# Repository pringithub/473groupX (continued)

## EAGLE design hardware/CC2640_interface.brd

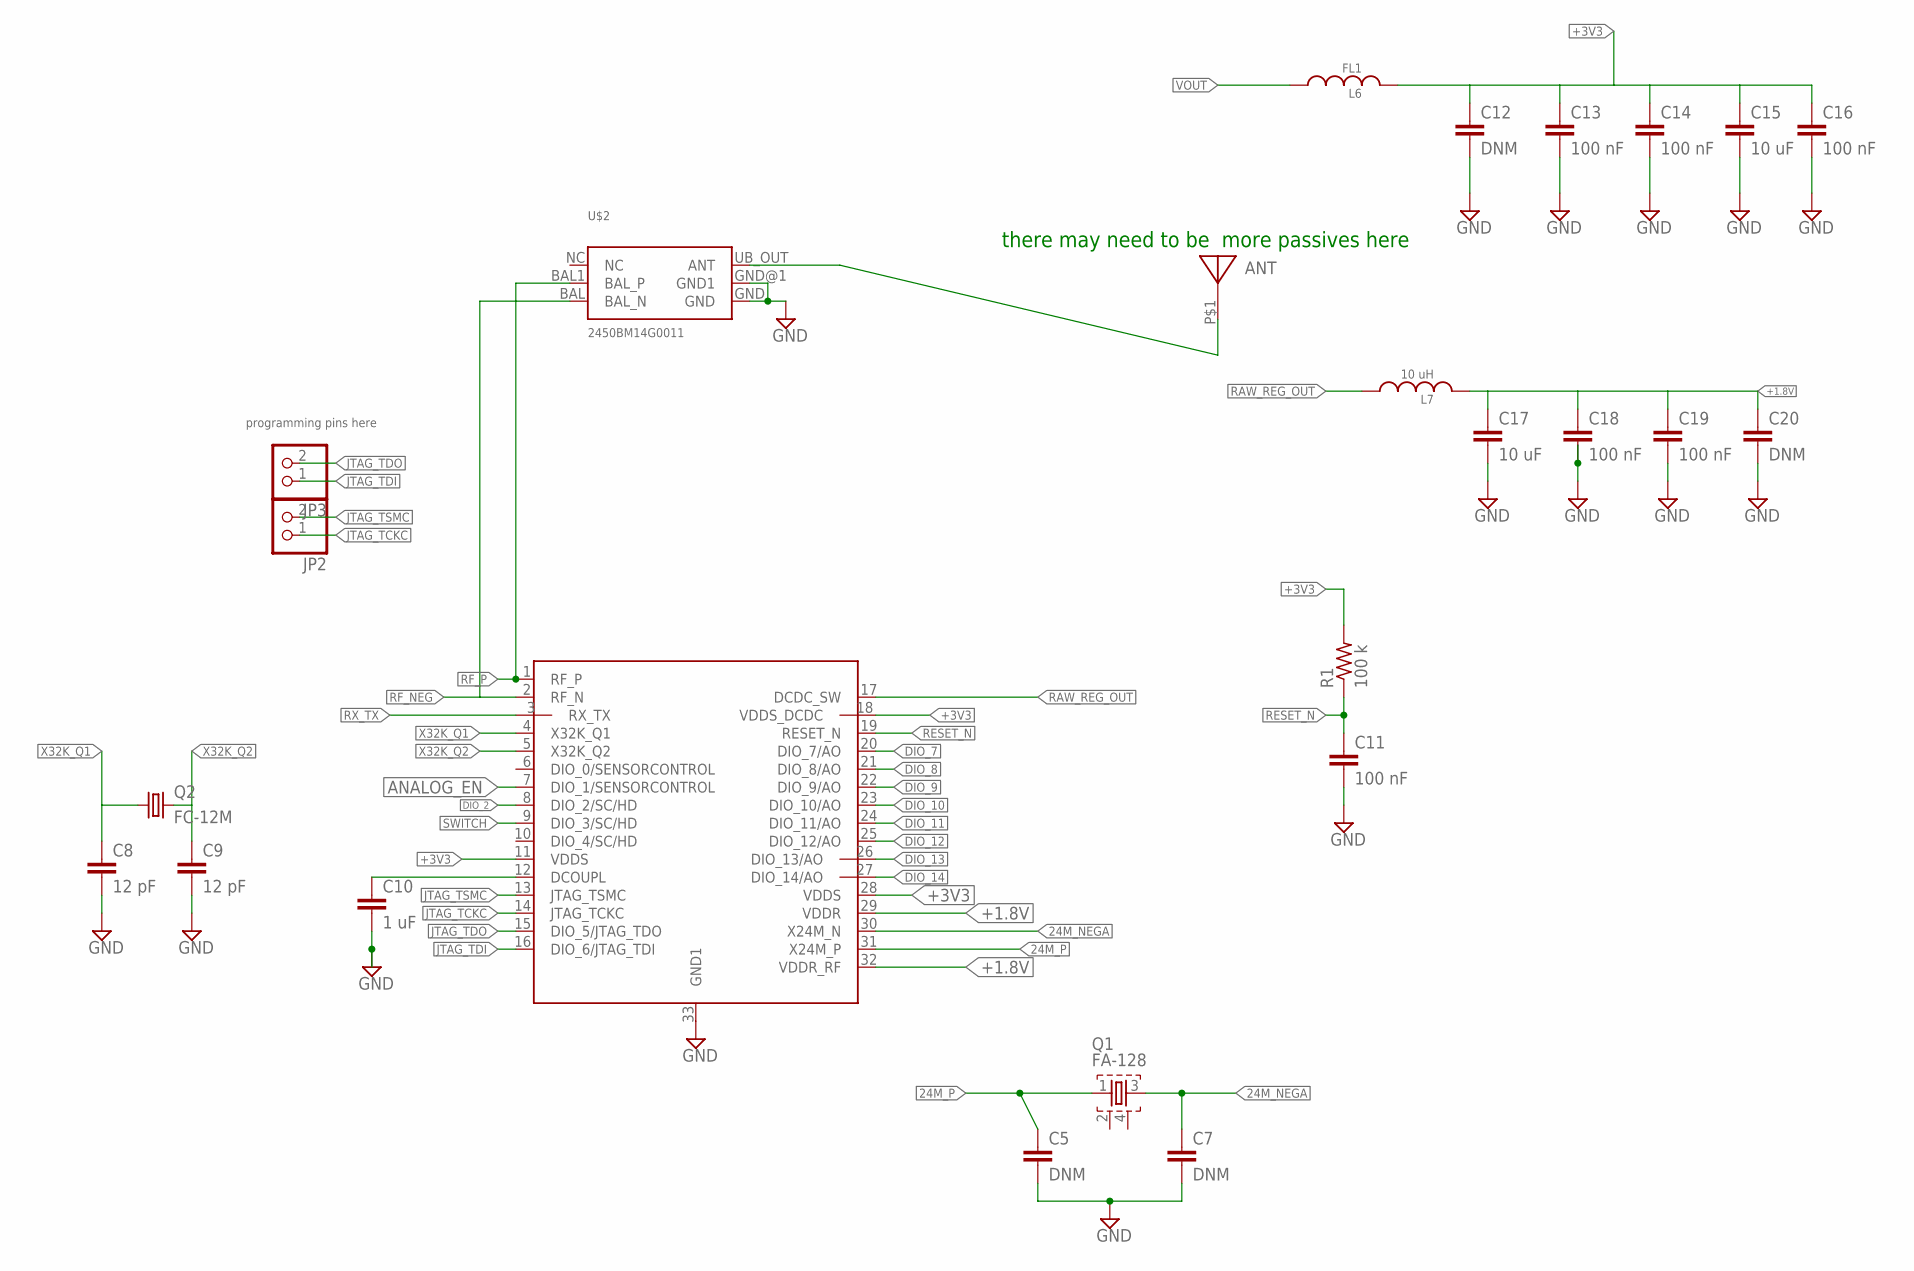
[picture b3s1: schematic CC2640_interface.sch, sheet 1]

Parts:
ANT: 2450AT18A100
C5, C7, C12, C20: DNM; C0402
C8, C9: 12 pF; C0402
C10: 1 uF; C0402
C11, C13, C14, C16, C18, C19: 100 nF; C0402
C15, C17: 10 uF; C0402
JP2, JP3: PINHD-1X2; 1X02
L6: FL1; 0603_CAP
L7: 10 uH; 0603_CAP
Q1: FA-128
Q2: FC-12M
R1: 100 k; R0402@1
U$1: CC2640-5MM; S-PVQFN-N32
U$2: 2450BM14G0011; DFN/LCC-6

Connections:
24M_NEGA: C7.1, Q1.3, U$1.30 (X24M_N)
24M_P: C5.1, Q1.1, U$1.31 (X24M_P)
+1.8V: C17.1, C18.1, C19.1, C20.1, L7.2, U$1.29 (VDDR), U$1.32 (VDDR_RF)
+3V3: C12.1, C13.1, C14.1, C15.1, C16.1, L6.2, R1.2, U$1.11 (VDDS), U$1.18 (VDDS_DCDC), U$1.28 (VDDS); also elsewhere on the board
ANALOG_EN: U$1.7 (DIO_1/SENSORCONTROL); also elsewhere on the board
DCOUPLE_ME: C10.1, U$1.12 (DCOUPL)
DIO_2: U$1.8 (DIO_2/SC/HD); also elsewhere on the board
DIO_7: U$1.20 (DIO_7/AO)
DIO_8: U$1.21 (DIO_8/AO)
DIO_9: U$1.22 (DIO_9/AO); also elsewhere on the board
DIO_10: U$1.23 (DIO_10/AO); also elsewhere on the board
DIO_11: U$1.24 (DIO_11/AO); also elsewhere on the board
DIO_12: U$1.25 (DIO_12/AO); also elsewhere on the board
DIO_13: U$1.26 (DIO_13/AO)
DIO_14: U$1.27 (DIO_14/AO); also elsewhere on the board
GND: C5.2, C7.2, C8.2, C9.2, C10.2, C11.2, C12.2, C13.2, C14.2, C15.2, C16.2, C17.2, C18.2, C19.2, C20.2, U$1.33 (GND1), U$2.GND, U$2.GND@1 (GND1); also elsewhere on the board
JTAG_TCKC: JP2.1, U$1.14 (JTAG_TCKC)
JTAG_TDI: JP3.1, U$1.16 (DIO_6/JTAG_TDI)
JTAG_TDO: JP3.2, U$1.15 (DIO_5/JTAG_TDO)
JTAG_TSMC: JP2.2, U$1.13 (JTAG_TSMC)
unnamed: ANT.P$1, U$2.UB_OUT (ANT)
RAW_REG_OUT: L7.1, U$1.17 (DCDC_SW)
RESET_N: C11.1, R1.1, U$1.19 (RESET_N)
RF_NEG: U$1.2 (RF_N), U$2.BAL (BAL_N)
RF_P: U$1.1 (RF_P), U$2.BAL1 (BAL_P)
RX_TX: U$1.3 (RX_TX)
SWITCH: U$1.9 (DIO_3/SC/HD); also elsewhere on the board
VOUT: L6.1; also elsewhere on the board
X32K_Q1: C8.1, Q2.1, U$1.4 (X32K_Q1)
X32K_Q2: C9.1, Q2.2, U$1.5 (X32K_Q2)

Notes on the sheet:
there may need to be more passives here
programming pins here

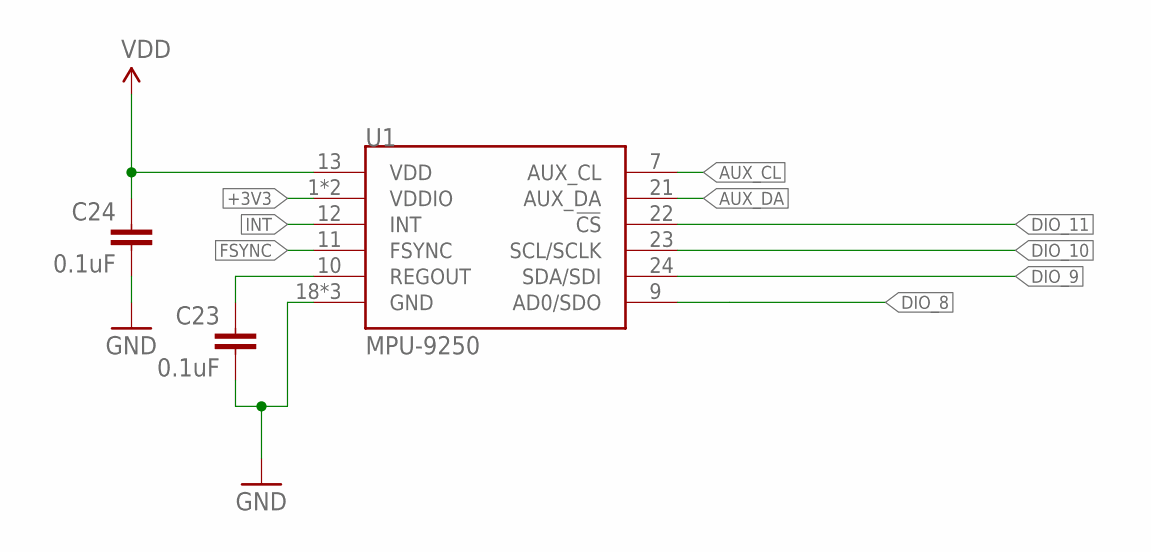
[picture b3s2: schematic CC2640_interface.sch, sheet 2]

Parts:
C23, C24: 0.1uF; 0603-CAP
U1: MPU-9250; QFN24_PAD

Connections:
+3V3: C24.1, U1.1 (VDDIO), U1.8 (VDDIO), U1.13 (VDD); also elsewhere on the board
ADSD_STUB: U1.9 (AD0/SDO)
AUX_CL: U1.7 (AUX_CL)
AUX_DA: U1.21 (AUX_DA)
DIO_9: U1.24 (SDA/SDI); also elsewhere on the board
DIO_10: U1.23 (SCL/SCLK); also elsewhere on the board
DIO_11: U1.22 (!CS); also elsewhere on the board
FSYNC: U1.11 (FSYNC)
GND: C23.2, C24.2, U1.18 (GND), U1.20 (GND), U1.CENTER (GND); also elsewhere on the board
INT: U1.12 (INT)
REGOUT: C23.1, U1.10 (REGOUT)

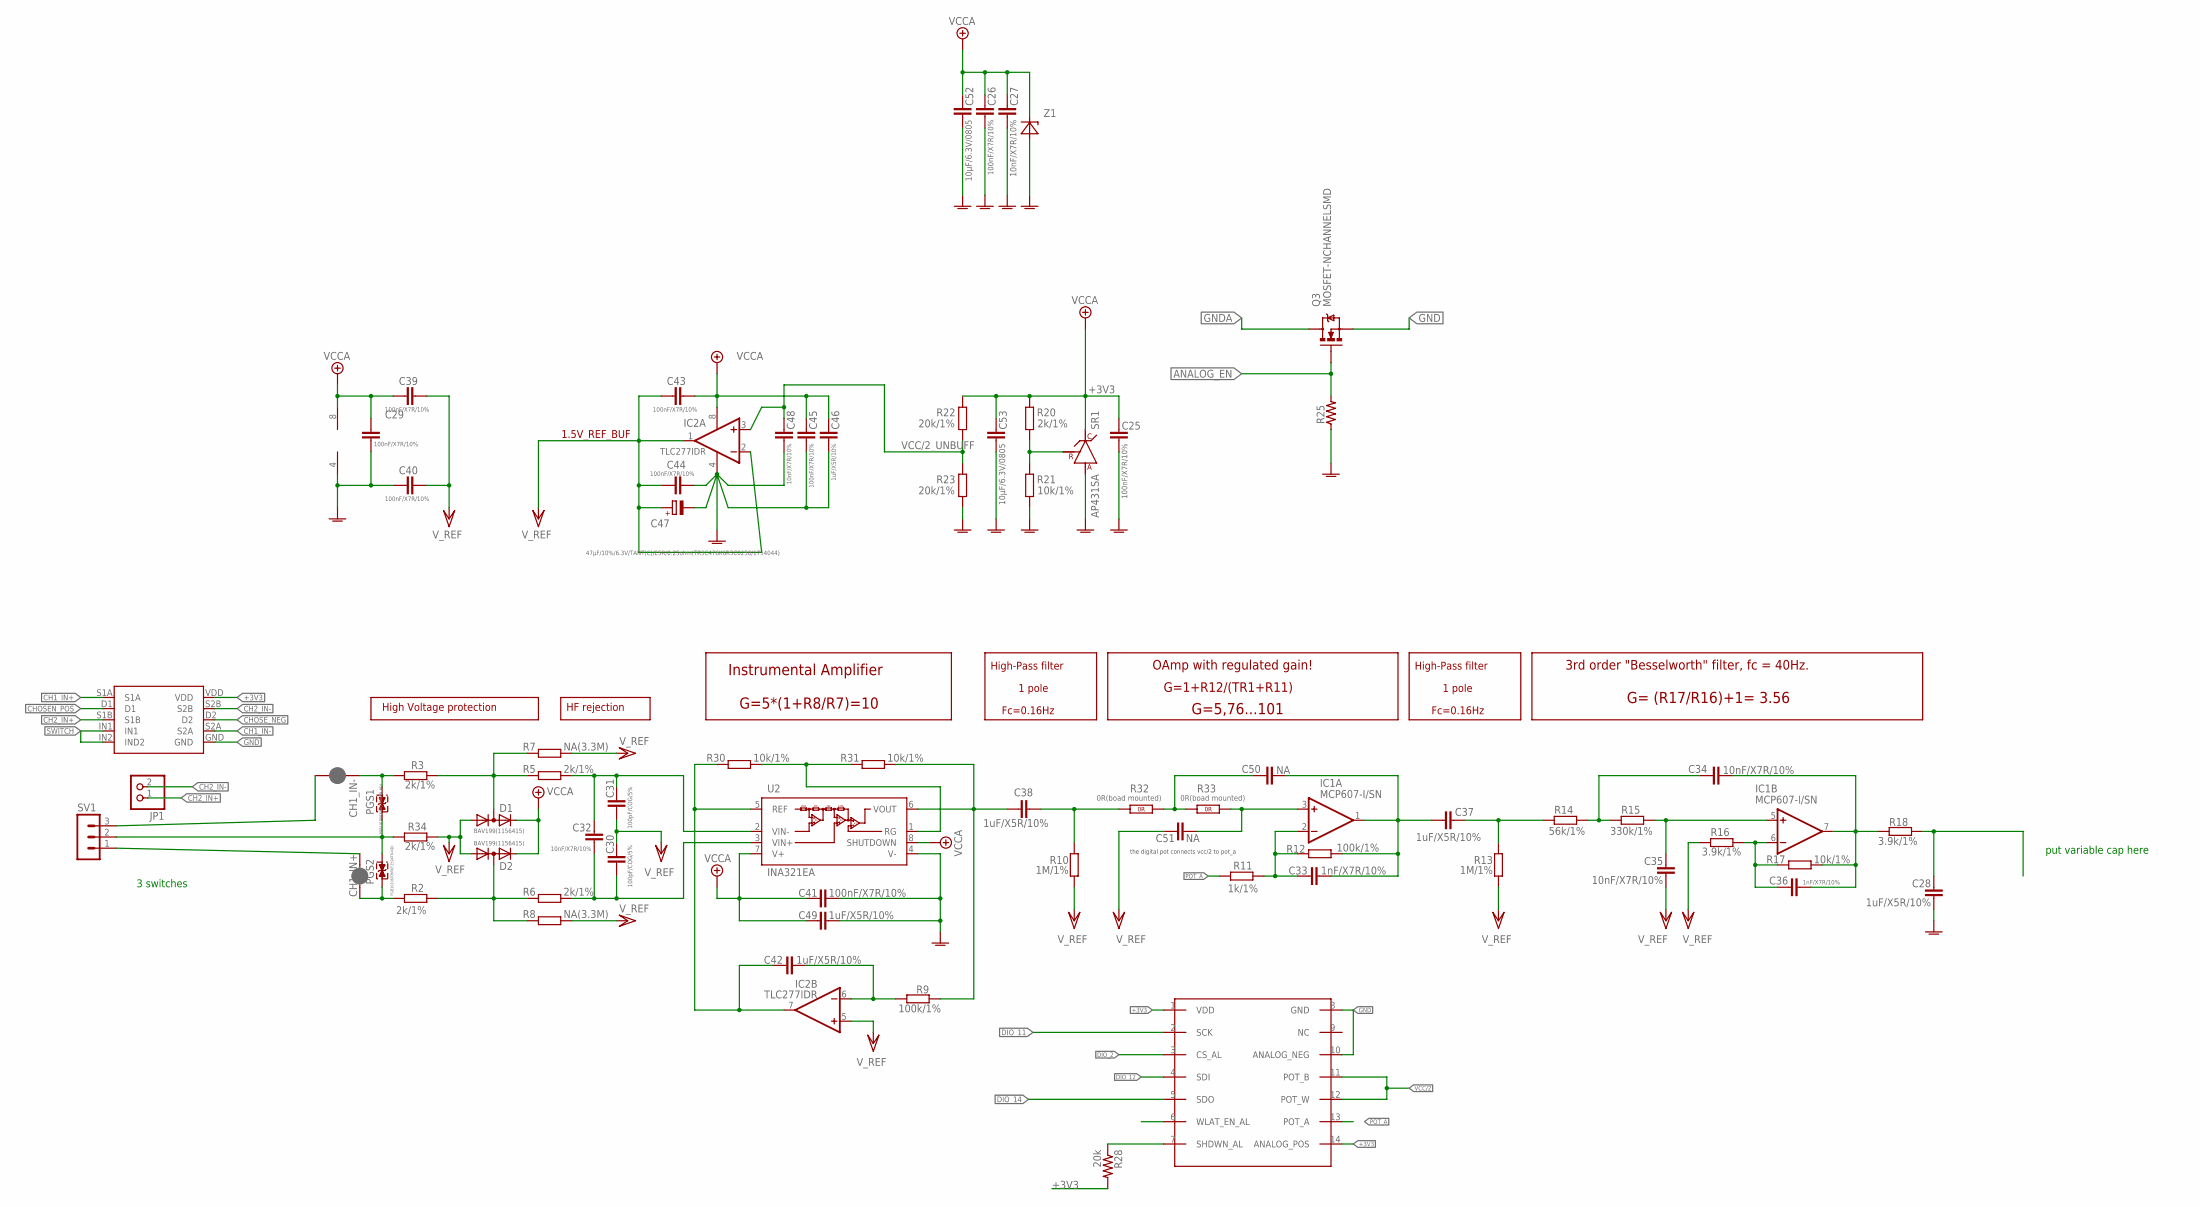
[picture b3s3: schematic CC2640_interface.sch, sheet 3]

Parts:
C25, C26, C29, C39, C40, C41, C43, C44, C45: 100nF/X7R/10%; C0603_DWS
C27, C32, C34, C35, C48: 10nF/X7R/10%; C0603_DWS
C28, C37, C38, C42, C46, C49: 1uF/X5R/10%; C0603_DWS
C30, C31: 100pF/COG/5%; C0603_DWS
C33, C36: 1nF/X7R/10%; C0603_DWS
C47: 47µF/10%/6.3V/TANT(C)/ESR/0.25ohm(TR3C476K6R3C025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; CT6032
C50, C51: NA; C0603_DWS_NA
C52, C53: 10µF/6.3V/0805; C0805_5MIL_DWS
D1, D2: BAV199(1156415); SOT23C(BAT54S)
DIG_POT: MCP41HVX1; TSSOP-14/5MM
IC1: MCP607-I/SN; SO08
IC2: TLC277IDR; SO08
JP1: PINHD-1X2; 1X02
PGS1, PGS2: PGB1010603MR(F2594TR-ND); 0603
Q3: MOSFET-NCHANNELSMD; SOT23-3
R2, R3, R5, R6, R20, R34: 2k/1%; R0603_5MIL_DWS
R7, R8: NA(3.3M); R0603_5MIL_DWS_NA
R9, R12: 100k/1%; R0603_5MIL_DWS
R10, R13: 1M/1%; R0603_5MIL_DWS
R11: 1k/1%; R0603_5MIL_DWS
R14: 56k/1%; R0603_5MIL_DWS
R15: 330k/1%; R0603_5MIL_DWS
R16, R18: 3.9k/1%; R0603_5MIL_DWS
R17, R21, R30, R31: 10k/1%; R0603_5MIL_DWS
R22, R23: 20k/1%; R0603_5MIL_DWS
R25: RESISTOR0603_RES; 0603-RES
R28: 20k; 0402-RES
R32, R33: 0R(boad mounted); 0603_0R
SJ1, SJ2: JUMPER-PAD-2-NC_BY_PASTEFULL-BOX-SILK; PAD-JUMPER-2-NC_BY_PASTE_YES_SILK_FULL_BOX
SR1: AP431SA; SOT-23
SV1: MA03-1
U2: INA321EA; MSOP8
U$3: ADG854; MINI_LFCSP
Z1: BZV55C6V2; MINI-MELF

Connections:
+3V3: C25.1, C26.1, C27.1, C29.1, C39.1, C41.1, C43.2, C45.1, C46.1, C49.1, C52.1, C53.1, D1.2 (K), D2.2 (K), DIG_POT.1 (VDD), DIG_POT.14 (ANALOG_POS), IC1.8 (V+), IC2.8 (V+), R20.2, R22.2, R28.2, SR1.1 (C), U2.7 (V+), U2.8 (SHUTDOWN), U$3.VDD, Z1.1 (C); also elsewhere on the board
ADC0: C28.1, R18.1
ANALOG_EN: Q3.1 (G), R25.2; also elsewhere on the board
CH1_IN+: SJ2.2, SV1.1, U$3.S1A
CH1_IN-: SJ1.1, SV1.3, U$3.S2A
CH2_IN+: JP1.1, U$3.S1B
CH2_IN-: JP1.2, U$3.S2B
CHOSEN_POS: PGS2.1, R2.1, SJ2.1, U$3.D1
CHOSE_NEG: PGS1.2, R3.1, SJ1.2, U$3.D2
DIO_2: DIG_POT.3 (CS_AL); also elsewhere on the board
DIO_11: DIG_POT.2 (SCK); also elsewhere on the board
DIO_12: DIG_POT.4 (SDI); also elsewhere on the board
DIO_14: DIG_POT.5 (SDO); also elsewhere on the board
GND: DIG_POT.8 (GND), DIG_POT.10 (ANALOG_NEG), Q3.2 (S), R25.1, U$3.GND; also elsewhere on the board
GNDA: C25.2, C26.2, C27.2, C28.2, C29.2, C40.1, C41.2, C44.2, C45.2, C46.2, C47.-, C48.2, C49.2, C52.2, C53.2, IC1.4 (V-), IC2.4 (V-), Q3.3 (D), R21.1, R23.1, SR1.3 (A), U2.4 (V-), Z1.2 (A)
unnamed: D1.3 (AK), R3.2, R5.2, R7.2
unnamed: D2.3 (AK), R2.2, R6.2, R8.2
unnamed: C42.2, IC2.7 (OUT), R30.2, U2.5 (REF)
unnamed: R30.1, R31.2, U2.1 (RG)
unnamed: R20.1, R21.2, SR1.2 (R)
unnamed: C38.2, R10.1, R32.1 (1.1)
unnamed: C50.1, R32.2 (1.2), R33.1 (1.1)
unnamed: PGS1.1, PGS2.2, R34.1, SV1.2
unnamed: C37.2, R13.1, R14.1
unnamed: C38.1, R9.2, R31.1, U2.6 (VOUT)
unnamed: C30.1, C32.1, R6.1, U2.3 (VIN+)
unnamed: C31.2, C32.2, R5.1, U2.2 (VIN-)
unnamed: C51.1, IC1.3 (+IN), R33.2 (1.2)
unnamed: C33.2, C37.1, C50.2, IC1.1 (OUT), R12.2
unnamed: C33.1, IC1.2 (-IN), R11.1, R12.1
unnamed: C35.1, IC1.5 (+IN), R15.2
unnamed: C34.1, R14.2, R15.1
unnamed: C34.2, C36.2, IC1.7 (OUT), R17.2, R18.2
unnamed: C36.1, IC1.6 (-IN), R16.1, R17.1
unnamed: C42.1, IC2.6 (-IN), R9.1
POT_A: DIG_POT.13 (POT_A), R11.2
SHDWN_AL: DIG_POT.7 (SHDWN_AL), R28.1
SWITCH: U$3.IN1, U$3.IN2 (IND2); also elsewhere on the board
VCC/2: C30.2, C31.1, C35.2, C39.2, C40.2, C43.1, C44.1, C47.+, C51.2, D1.1 (A), D2.1 (A), DIG_POT.11 (POT_B), DIG_POT.12 (POT_W), IC2.1 (OUT), IC2.2 (-IN), IC2.5 (+IN), R7.1, R8.1, R10.2, R13.2, R16.2, R34.2
VCC/2_UNBUFF: C48.1, IC2.3 (+IN), R22.1, R23.2

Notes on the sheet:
G=1+R12/(TR1+R11)
G=5,76...101
3rd order "Besselworth" filter, fc = 40Hz.
Fc=0.16Hz
HF rejection
High Voltage protection
High-Pass filter
OAmp with regulated gain!
G= (R17/R16)+1= 3.56
1 pole
G=5*(1+R8/R7)=10
1.5V_REF_BUF
Instrumental Amplifier
the digital pot connects vcc/2 to pot_a
put variable cap here
3 switches

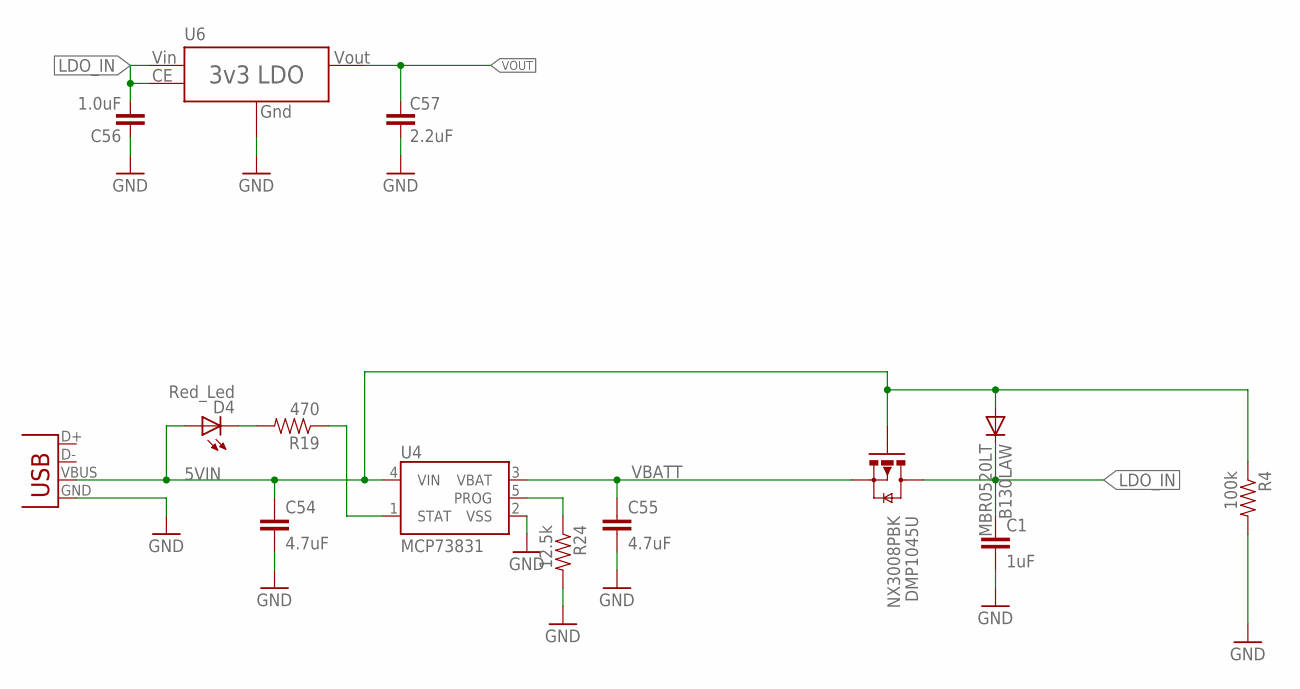
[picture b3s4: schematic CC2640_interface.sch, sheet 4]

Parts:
B130LAW: MBR0520LT; SOD123
C1: 1uF; 0402-CAP
C54, C55: 4.7uF; 0402-CAP
C56: 1.0uF; C0805
C57: 2.2uF; C0805
D4: Red_Led; LED-0603
DMP1045U: NX3008PBK; SOT23-3
R4: 100k; 0402-RES
R19: 470; 0402-RES
R24: 12.5k; 0402-RES
U4: MCP73831; SOT23-5
U6: XC6210; SOT-25
X1: USB-MICROB

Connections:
5VIN: B130LAW.A, C54.1, D4.A, DMP1045U.1 (G), R4.1, U4.4 (VIN), X1.VBUS
GND: C1.2, C54.2, C55.2, C56.1, C57.2, R4.2, R24.2, U4.2 (VSS), U6.2 (GND), X1.GND; also elsewhere on the board
LDO_IN: B130LAW.C, C1.1, C56.2, DMP1045U.3 (D), U6.1 (VIN), U6.3 (CE)
unnamed: R24.1, U4.5 (PROG)
unnamed: D4.C, R19.2
unnamed: R19.1, U4.1 (STAT)
VBATT: C55.1, DMP1045U.2 (S), U4.3 (VBAT)
VOUT: C57.1, U6.5 (VOUT); also elsewhere on the board

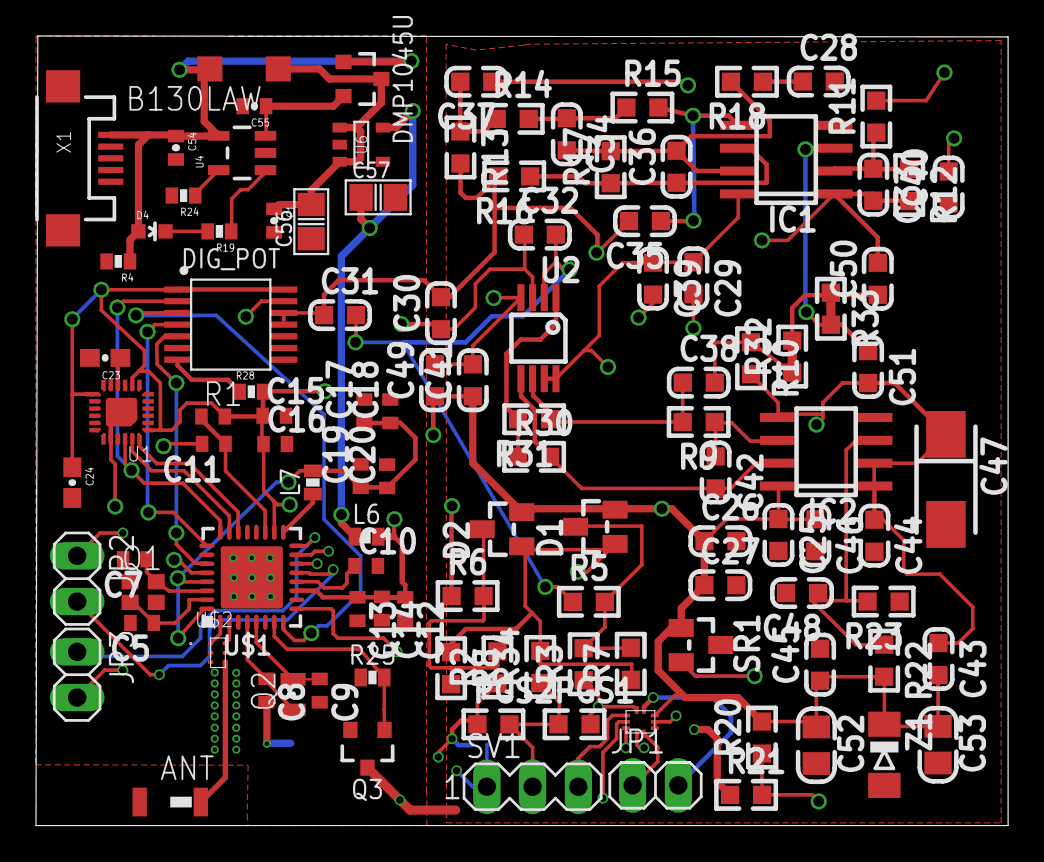
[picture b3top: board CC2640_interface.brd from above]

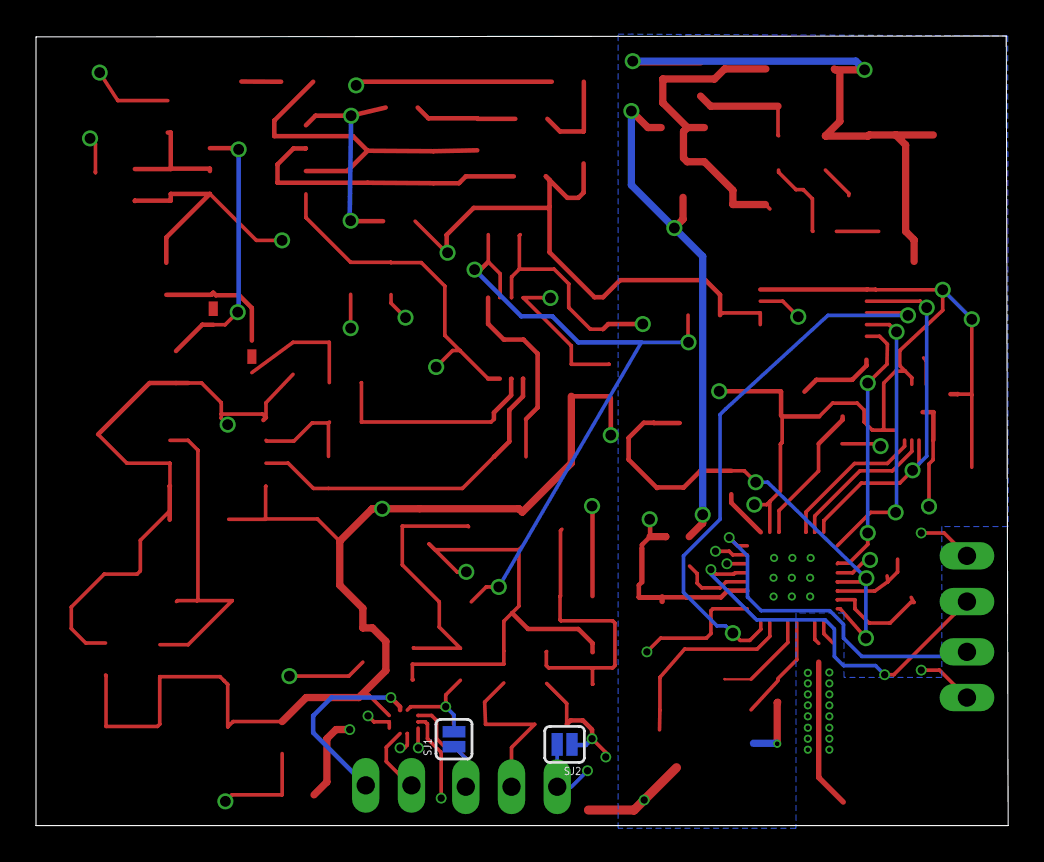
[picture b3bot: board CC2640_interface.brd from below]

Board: 4 copper layers, 54.0 x 43.9 mm, 114 parts (2 on the bottom side), 65 nets.

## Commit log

2016-10-11 added emg.ino
2016-10-16 added pulse width calc to emg_arduino
2016-10-17 CC2650 CCS Project for FlexZone BLE connectivity
    Code Composer project for TI's CC2650 Launchpad kit.
    - The project advertises as BLE peripherals (name FlexZone).
    - It exposes three services, one Standard DIS service and two other custom services
    - First custom service is for notifying 2/3 bytes of EMG data. Second custom service notifies 3 bytes of x,y,z accelerometer data.
    - This commit has only dummy data going to these services using Button 1 for EMG and Button 2 for Acceleromter.
    - The device readvertises after BLE disconnection.
2016-10-20 hardware and imu added
2016-10-23 first rev done except antenna, antennas make a dude sad
2016-10-26 added .c/.h files, interfaced some ish
2016-10-30 Added ignores for CCS workspace required files/dirs
2016-10-31 we are shipping this
2016-10-31 changed some things
2016-11-03 Init CCS workspace
2016-11-03 ignore more stuff
2016-11-03 Done with all of the ignores... lololol
2016-11-03 added partial emg driver, random heartbeat task to test stuffz
2016-11-03 Removed top level CCS Project folders
2016-11-03 fixed merge conflict
2016-11-03 updated antenna, split HW into MYO and OLIMEX
2016-11-05 final rev
2016-11-08 added MPU2690 support, fixed comments, mpu docs
    Need to build MPU data analysis in Accel task
2016-11-08 added UART logging
2016-11-10 updated emg.ino
2016-11-10 EMG WORKS BITCHESSSSSSS
2016-11-10 cross-thread LED support for debugging
    can be used to show missed deadlines
2016-11-10 memory improvements & added timing support
2016-11-10 emg data processing timing
2016-11-10 added a line lol
2016-11-10 some more stuff
    globalized emg stats struct, removed heartbeat, moved led init to main,
    changed scope of repcount so is persistent across calls
2016-11-14 BLE integration
2016-11-14 Compiled executable. Good for debugging.
2016-11-14 Fixed RTOS booting from flash issue
2016-11-15 added SolidWorks case
2016-11-15 someone port this to the 26xx
2016-11-15 Testing project for Digipot & blinky
2016-11-15 added target configs for cc2640 on main project.
    doesnt work yet luls
2016-11-16 Test CC2640 project with digipot
2016-11-16 some changes on dev platform
2016-11-16 integrated adc & digipots on PCB
2016-11-16 updated readmes
2016-11-30 dev & pcb workspaces, i2c imu, cc2640 porting
2016-12-02 further ble integration
2016-12-02 hardware i/o config
2016-12-02 fixed imu
2016-12-02 moar imu stuff
2016-12-03 board file and memory saving stuff
2016-12-03 threshold and stack size changes
2016-12-06 switched analog_en to active_, two channels for adc
2016-12-07 digipot & vibe motor stuff
2016-12-07 main processing loop stuff
2016-12-08 some fuck shit idk nothing works
2016-12-08 everything works but imu and haptic
2016-12-08 imu and haptic feedbacl
2016-12-08 shortened ble packet send length
2016-12-08 last not working copy
2016-12-08 bleh
2017-01-02 one last one for the ages boys
